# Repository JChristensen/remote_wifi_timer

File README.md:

# Remote WiFi Timer  
https://github.com/JChristensen/remote_wifi_timer  
README file  
Jack Christensen  
Oct-2025

## License
  
This work is licensed under the [Creative Commons Attribution-ShareAlike 4.0 International License](https://creativecommons.org/licenses/by-sa/4.0/).

## See also
[Main control program.](https://github.com/JChristensen/timer_main)  
[Microcontroller firmware.](https://github.com/JChristensen/timer_remote)  
[A small PCB for the LEDs and pushbutton.](https://github.com/JChristensen/ac-timer-panel)

## Overview
This is the printed circuit board for the remote timer units. For an overall description of the project, see [the main control program repo](https://github.com/JChristensen/timer_main).

A Bill of Materials is available in this repo and also [on Mouser.com](https://www.mouser.com/Tools/Project/Share?AccessID=4ef4109354).

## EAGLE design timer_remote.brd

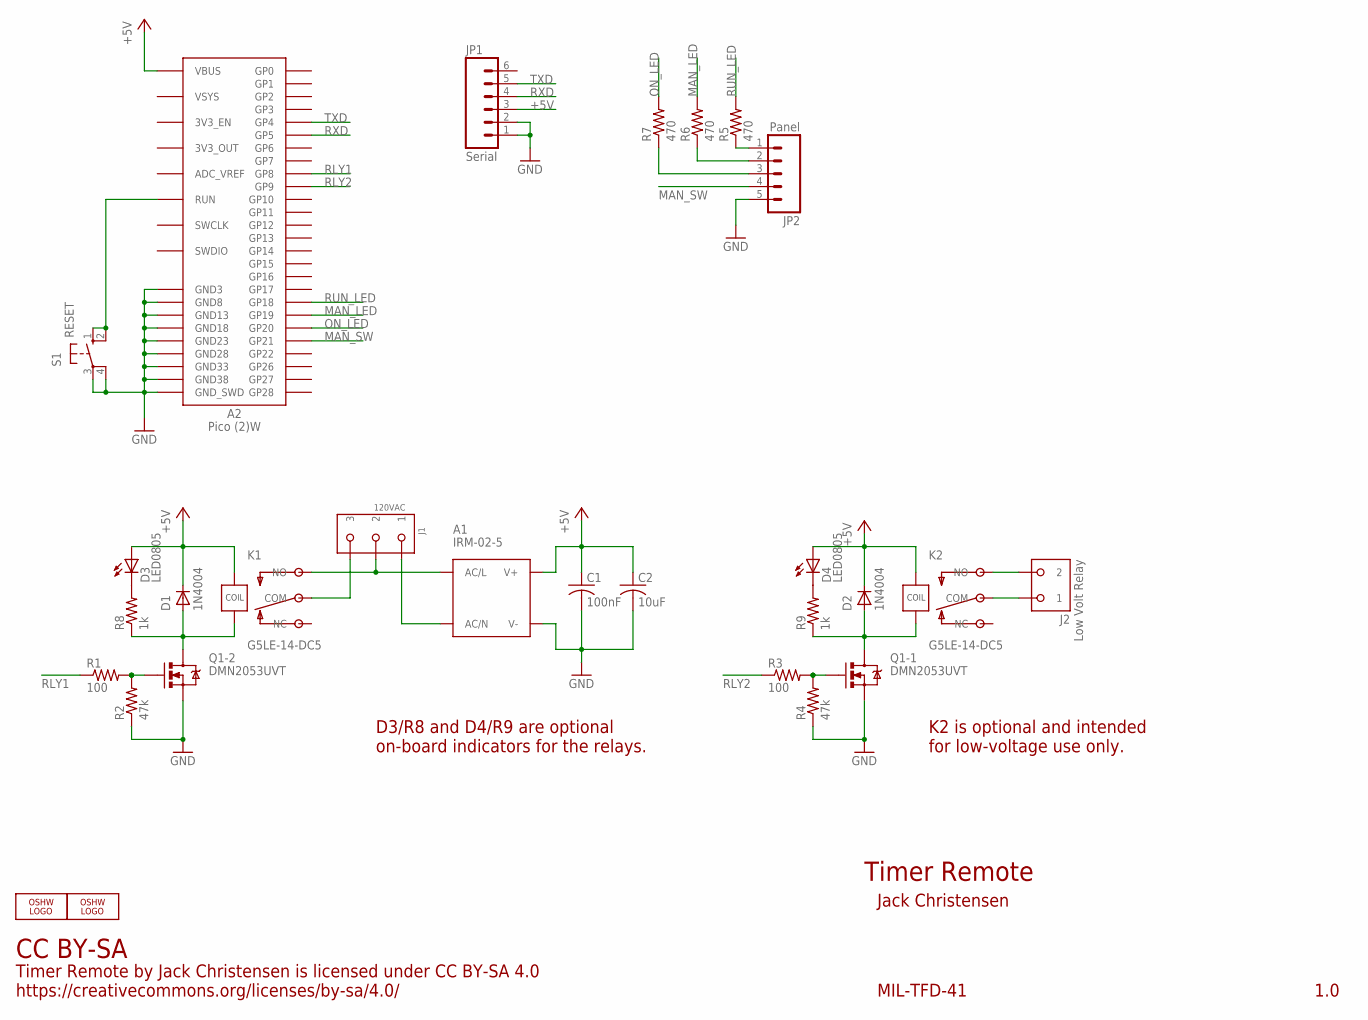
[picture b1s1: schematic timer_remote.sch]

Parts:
A1: IRM-02-5; IRM-01
A2: Pico (2)W; PICO
C1: 100nF; M0805
C2: 10uF; M0805
D1, D2: 1N4004; 1N400X
D3: LED0805; D0805A
D4: LED0805; D0805
J1: 120VAC; OST-TB-3-0.20
J2: Low Volt Relay; OST-TB-2-0.20
JP1: Serial; 1X06_LOCK
JP2: Panel; 1X05_LOCK
K1, K2: G5LE-14-DC5; NAIS-JS1-5V
LOGO1, LOGO2: OSHW_LOGO_10MILX0200-NT; OSHW_10X200_NOTEXT
Q1: DMN2053UVT; SOT23-6
R1, R3: 100; M0805
R2, R4: 47k; M0805
R5, R6, R7: 470; M0805
R8, R9: 1k; M0805
S1: RESET; B3F-10XXOCT

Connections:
+5V: A1.V+, A2.P$40 (VBUS), C1.1, C2.1, D1.K, D2.K, D3.A, D4.A, JP1.3, K1.C1, K2.C1
GND: A1.V-, A2.P$03 (GND3), A2.P$08 (GND8), A2.P$13 (GND13), A2.P$18 (GND18), A2.P$23 (GND23), A2.P$28 (GND28), A2.P$33 (GND33), A2.P$38 (GND38), A2.P$SWGND (GND_SWD), C1.2, C2.2, JP1.1, JP1.2, JP2.5, Q1.2 (S), Q1.5 (S), R2.1, R4.1, S1.3, S1.4 (P1)
MAN_LED: A2.P$25 (GP19), R6.2
MAN_SW: A2.P$27 (GP21), JP2.4
unnamed: J2.P$2 (2), K2.NO
unnamed: J2.P$1 (1), K2.COM
unnamed: Q1.1 (G), R3.2, R4.2
unnamed: D2.A, K2.C2, Q1.6 (D), R9.1
unnamed: A2.P$30 (RUN), S1.1 (S), S1.2 (S1)
unnamed: D1.A, K1.C2, Q1.4 (D), R8.1
unnamed: A1.AC/L, J1.P$2 (2), K1.NO
unnamed: A1.AC/N, J1.P$1 (1)
unnamed: J1.P$3 (3), K1.COM
unnamed: Q1.3 (G), R1.2, R2.2
unnamed: JP2.1, R5.1
unnamed: D3.K (C), R8.2
unnamed: JP2.2, R6.1
unnamed: JP2.3, R7.1
unnamed: D4.K (C), R9.2
ON_LED: A2.P$26 (GP20), R7.2
RLY1: A2.P$11 (GP8), R1.1
RLY2: A2.P$12 (GP9), R3.1
RUN_LED: A2.P$24 (GP18), R5.2
RXD: A2.P$07 (GP5), JP1.4
TXD: A2.P$06 (GP4), JP1.5

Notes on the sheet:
Timer Remote
CC BY-SA
Jack Christensen
MIL-TFD-41
1.0
Timer Remote by Jack Christensen is licensed under CC BY-SA 4.0 https://creativecommons.org/licenses/by-sa/4.0/
D3/R8 and D4/R9 are optional on-board indicators for the relays.
K2 is optional and intended for low-voltage use only.

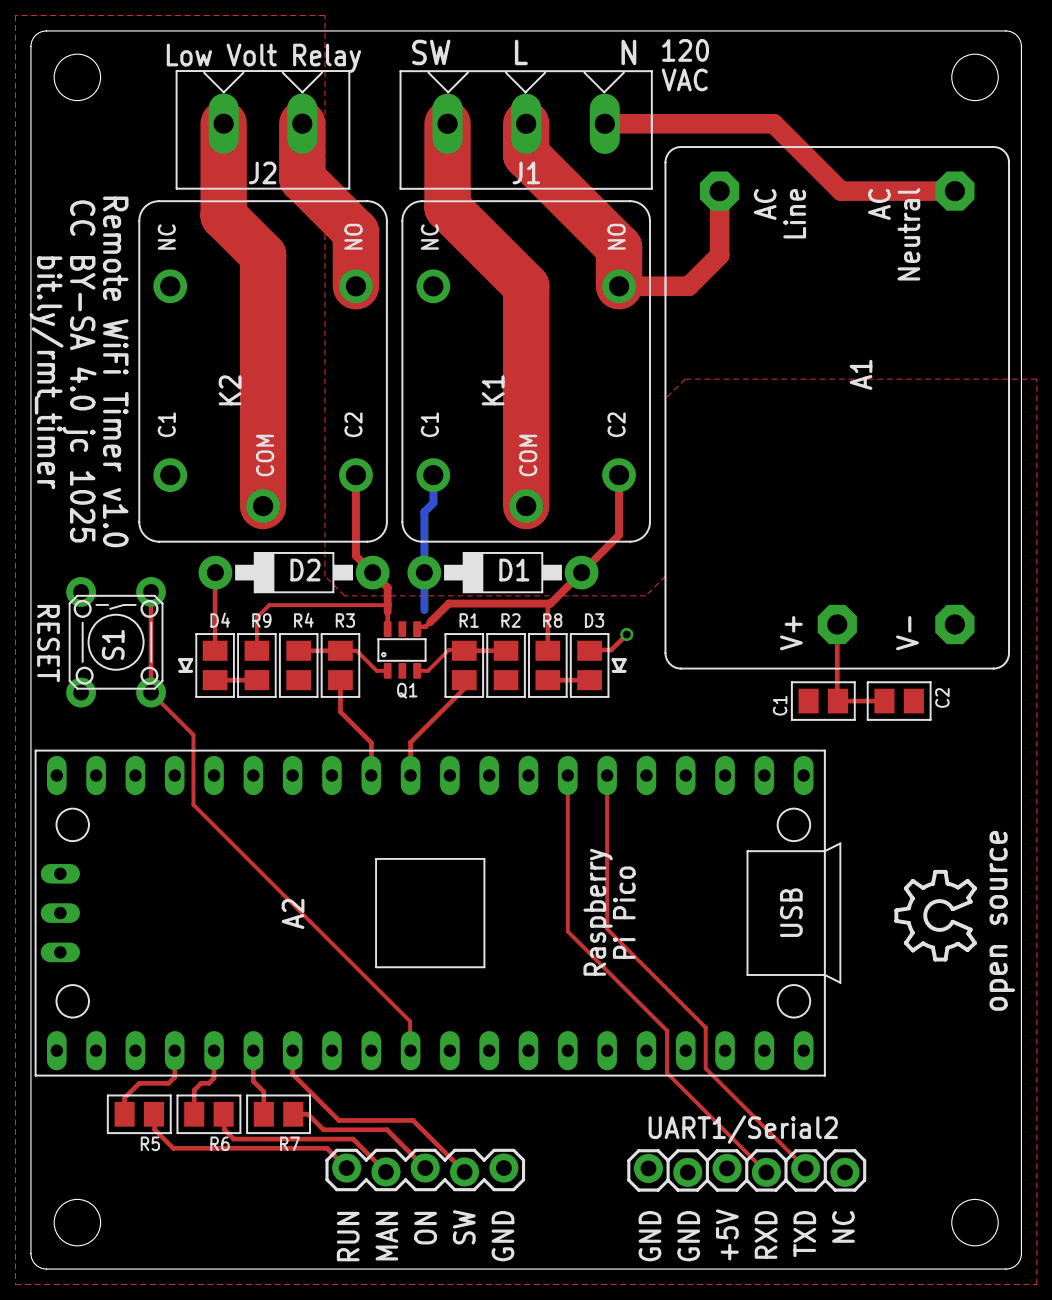
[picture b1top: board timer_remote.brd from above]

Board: 2 copper layers, 64.0 x 80.0 mm, 27 parts (1 on the bottom side), 25 nets.

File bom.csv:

Remote WiFi Timer,,,,,,,
https://github.com/JChristensen/remote_wifi_timer,,,,,,,
Bill of Materials,,,,,,,
,,,,,,,
Part,Qty,Value,Description,Manufacturer,Mfr_Part_ Nbr,Mouser_Part_Nbr,Notes
A1,1,IRM-02-5,"Power Supply, 2W 5V 400mA",Mean Well,IRM-02-5,709-IRM02-5,
A2,1,Pico (2)W,Pico2W microcontroller,Raspberry Pi,SC1633,358-SC1633,Or PicoW.
C1,1,100nF,MLCC 50V 0.1uF X5R or X7R 0805,KAM21BR71H104JT,581-KAM21BR71H104JT,581-KAF21BR71H104JM,Or equivalent.
C2,1,10uF,MLCC 6.3V 10uF X5R or X7R 0805,KYOCERA AVX,KGM21AR50J106KU,581-KGM21AR50J106KU,Or equivalent.
"D1, D2",2,1N4004,1A 400V Standard rectifier,On Semi,1N4004RLG,863-1N4004RLG,Or equivalent. D2 optional if K2 not installed.
"D3, D4",3,LTST-C171YKT,"SMT LED, 0805",LITEON,LTST-C171YKT,859-LTST-C171YKT,Or equivalent. Optional onboard indicators.
J1,1,1935174,"5mm Terminal Block, 3 Position",Phoenix Contact,1935174,651-1935174,
J2,1,1935161,"5mm Terminal Block, 2 Position",Phoenix Contact,1935161,651-1935161,
"K1, K2",2,,Power Relay SPDT Sealed 5VDC,Omron,G5LE-14-DC5,653-G5LE-14-DC5,K2 is optional.
Q1,1,DMN2053UVT-7,Dual MOSFET,Diodes Incorporated,DMN2053UVT-7,621-DMN2053UVT-7,
"R1, R3",2,100Ω,"Thick film resistor, 0805, 0.25W, 1%",KOA Speer,RK73H2ATTD1000F,660-RK73H2ATTD1000F,Or equivalent. R3 optional if K2 not installed.
"R2, R4",2,47kΩ,"Thick film resistor, 0805, 0.25W, 1%",KOA Speer,RK73H2ATTD4702F,660-RK73H2ATTD4702F,Or equivalent.
"R5, R6, R7",3,470Ω,"Thick film resistor, 0805, 0.25W, 1%",KOA Speer,RK73H2ATTD4700F,660-RK73H2ATTD4700F,Or equivalent.
"R8, R9",2,1kΩ,"Thick film resistor, 0805, 0.25W, 1%",KOA Speer,RK73H2ATTD1001F,660-RK73H2ATTD1001F,"Or equivalent. Optional if D3, D4 not installed."
S1,1,,Tactile button switch,Omron,B3F-1022,653-B3F-1022,Or equivalent.

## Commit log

2025-10-04 Initial commit.
2025-10-04 Update README.
2025-10-07 Sent to fab.
2025-12-04 Minor tweaks to PCB traces, update README, BoM, images.

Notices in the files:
timer_remote.brd:
CC BY-SA 4.0 jc 1025
parts and their libraries:
SparkFun: Licensing: CC v3.0 Share-Alike You are welcome to use this library for commercial purposes.
